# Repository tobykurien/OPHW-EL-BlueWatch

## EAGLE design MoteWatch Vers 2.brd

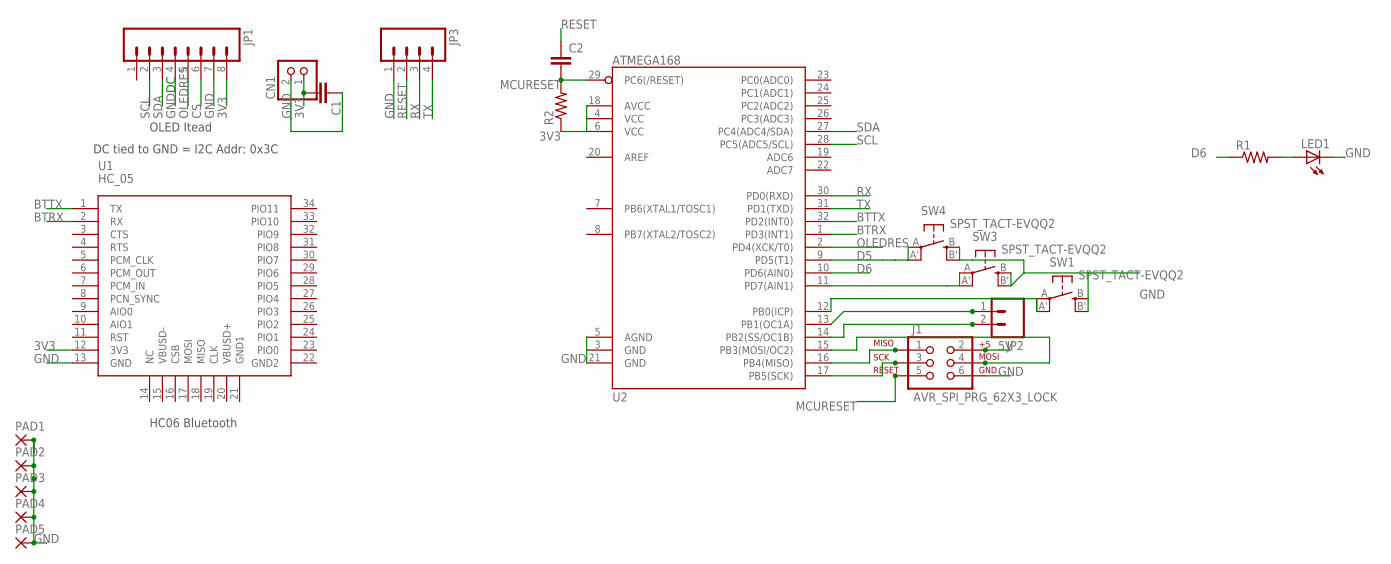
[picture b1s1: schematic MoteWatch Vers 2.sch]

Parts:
C1, C2: CAP1206; 1206
CN1: JST_2PIN-THM-RA; JST-PH-2-THM-RA
J1: AVR_SPI_PRG_62X3_LOCK; 2X3_LOCK
JP1: M08LOCK; 1X08_LOCK
JP2: M02LOCK; 1X02_LOCK
JP3: M04PTH; 1X04
LED1: LED1206; LED-1206
PAD1, PAD2, PAD3, PAD4, PAD5: SMD5; SMD2,54-5,08
R1, R2: RESISTOR1206; 1206
SW1, SW3, SW4: SPST_TACT-EVQQ2; EVQ-Q2
U1: HC_05; BLUETOOTH_SMD
U2: ATMEGA168; TQFP32-08

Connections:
3V3: C1.2, CN1.1 (2), JP1.8, R2.1, U1.12 (3V3), U2.4 (VCC), U2.6 (VCC), U2.18 (AVCC)
5V: J1.2
BTRX: U1.2 (RX), U2.1 (PD3(INT1))
BTTX: U1.1 (TX), U2.32 (PD2(INT0))
CS: JP1.6
D5: SW4.A, SW4.A' (P1), U2.9 (PD5(T1))
D6: R1.1, U2.10 (PD6(AIN0))
D7: SW3.A, SW3.A' (P1), U2.11 (PD7(AIN1))
D8: SW1.A, SW1.A' (P1), U2.12 (PB0(ICP))
D9: JP2.1, U2.13 (PB1(OC1A))
D10: JP2.2, U2.14 (PB2(SS/OC1B))
GND: C1.1, CN1.2 (1), J1.6, JP1.4, JP1.7, JP3.1, LED1.C, PAD1.1, PAD2.1, PAD3.1, PAD4.1, PAD5.1, SW1.B (S), SW1.B' (S1), SW3.B (S), SW3.B' (S1), SW4.B (S), SW4.B' (S1), U1.13 (GND), U2.3 (GND), U2.5 (AGND), U2.21 (GND)
MCURESET: C2.2, J1.5, R2.2, U2.29 (PC6(/RESET))
MISO: J1.1, U2.16 (PB4(MISO))
MOSI: J1.4, U2.15 (PB3(MOSI/OC2))
unnamed: LED1.A, R1.2
OLEDRES: JP1.5, U2.2 (PD4(XCK/T0))
RESET: C2.1, JP3.2
RX: JP3.3, U2.30 (PD0(RXD))
SCK: J1.3, U2.17 (PB5(SCK))
SCL: JP1.2, U2.28 (PC5(ADC5/SCL))
SDA: JP1.3, U2.27 (PC4(ADC4/SDA))
TX: JP3.4, U2.31 (PD1(TXD))

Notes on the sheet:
DC tied to GND = I2C Addr: 0x3C
OLED Itead
HC06 Bluetooth

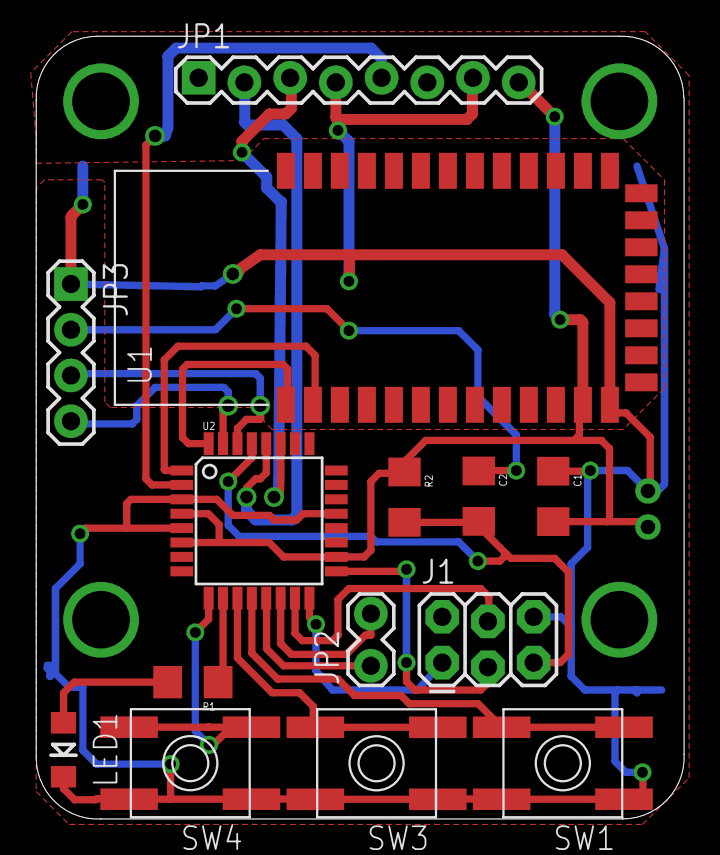
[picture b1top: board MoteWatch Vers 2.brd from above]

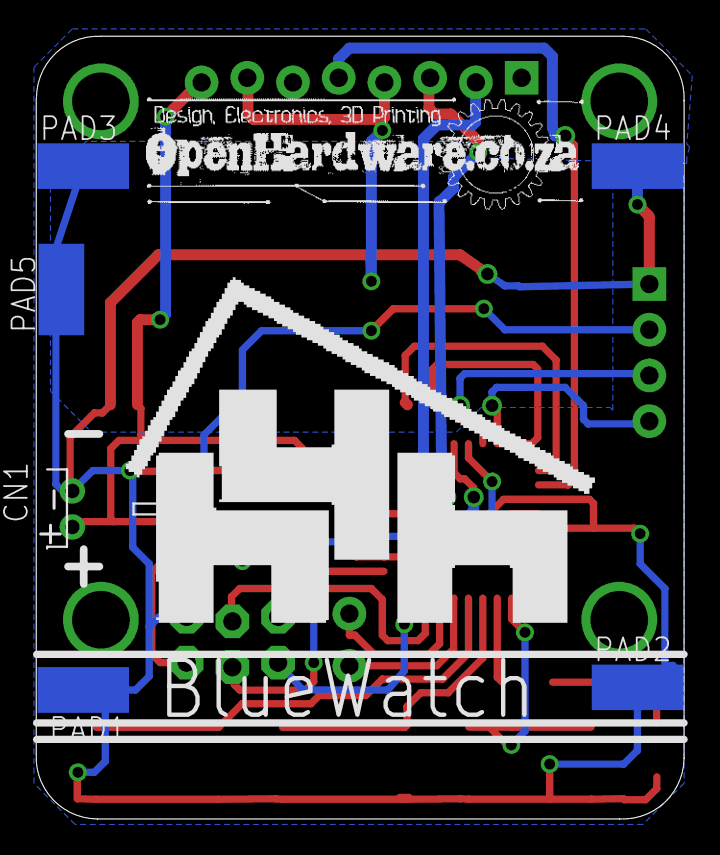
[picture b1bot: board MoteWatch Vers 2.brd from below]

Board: 2 copper layers, 36.0 x 43.5 mm, 20 parts (6 on the bottom side), 21 nets.

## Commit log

2014-05-25 Uploaded firmware as used to test v0.2 watches
2014-06-09 Revision for second order
2014-06-16 Firmware as tested
    Firmware as installed on Rev 2 prototypes delivered to H4H this week
2014-08-26 first commit, working bluetooth, LCD, and serial
2014-08-26 fixed button by enabling internal pullup on pin 5
2014-08-27 initial comms between watch an app
2014-08-27 implemented sending frame buffer from app to watch
2014-08-27 sending of android view to watch display working
2014-08-27 independent scaling of watch display view between app and watch
2014-08-27 added comments to the confusing bits
2014-08-27 changed display to time and added display timeout
2014-08-27 added button presses to watch state
2014-08-28 fixed display timeout, refactored code to run as a service rather than from activity. First usable watch functionality.
2014-08-28 fixed display timeout issues, added watch status to notification
2014-08-28 fixed off-by-one error in frame buffer converter
2014-08-28 more comments and removed exception swallowing in sendFrameBuffer()
2014-08-28 better clock preview
2014-08-28 added readme with reference links
2014-08-28 moved files to better locations
2014-08-29 fixed crash if bluetooth is off
2014-08-29 created watch modules with 2 clock faces
2014-08-29 selectable watch faces
2014-08-29 added bluetooth timeout when waiting for frame buffer
2014-08-29 added House4Hack Entry module, added support for module switching with middle button, and primary/secondary action with other buttons
2014-08-29 fixed buttons being sent on wakeup, changed to always wake up to the clock
2014-08-29 changed House4Hack module to use a layout file
2014-08-29 fixed hour hand
2014-09-01 added GPL license
2014-09-02 added bluetooth reconnect, better bluetooth handling
2014-09-02 v0.01-alpha release
2014-09-02 added v0.01-alpha apk
2014-09-03 added module preferences ability, added settings for digital clock 1
2014-09-03 added 12/24 hour clock option
2014-09-03 linked to SHAC app
2014-09-03 support for more than one module when switching modules/clock
2014-09-03 added accessibility service to read notifications
2014-09-03 added notifications module, still buggy
2014-09-03 small fixes
2014-09-09 moved accessibility flag to service

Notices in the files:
parts and their libraries:
SparkFun-Passives: Licensing: CC v3.0 Share-Alike You are welcome to use this library for commercial purposes.
